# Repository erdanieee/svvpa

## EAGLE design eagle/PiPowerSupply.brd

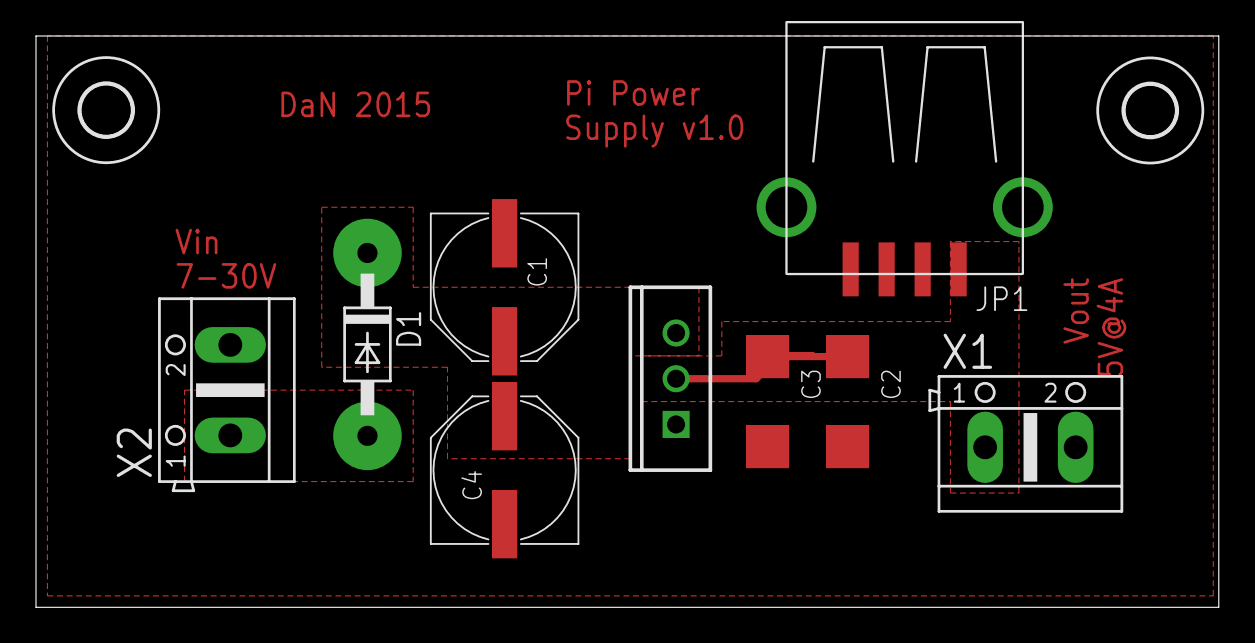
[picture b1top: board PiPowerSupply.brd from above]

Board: 2 copper layers, 65.7 x 31.7 mm, 11 parts (0 on the bottom side), 4 nets.

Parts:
C1, C4: 10u; PANASONIC_E
C2, C3: 10u; SMC_C
D1: 1N4004; DO41-10
H1, H2: MOUNT-HOLE2.8; 2,8
JP1: USB-A-S
U$1: V_REG_317SINK; TO220-ADJ
X1, X2: AK500/2

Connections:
GND: C1.-, C2.-, C3.-, C4.-, JP1.GND, U$1.ADJ, X1.2, X2.2
unnamed: D1.A, X2.1
VIN: C1.+, C4.+, D1.C, U$1.IN
VOUT: C2.+, C3.+, JP1.VBUS, U$1.OUT, X1.1

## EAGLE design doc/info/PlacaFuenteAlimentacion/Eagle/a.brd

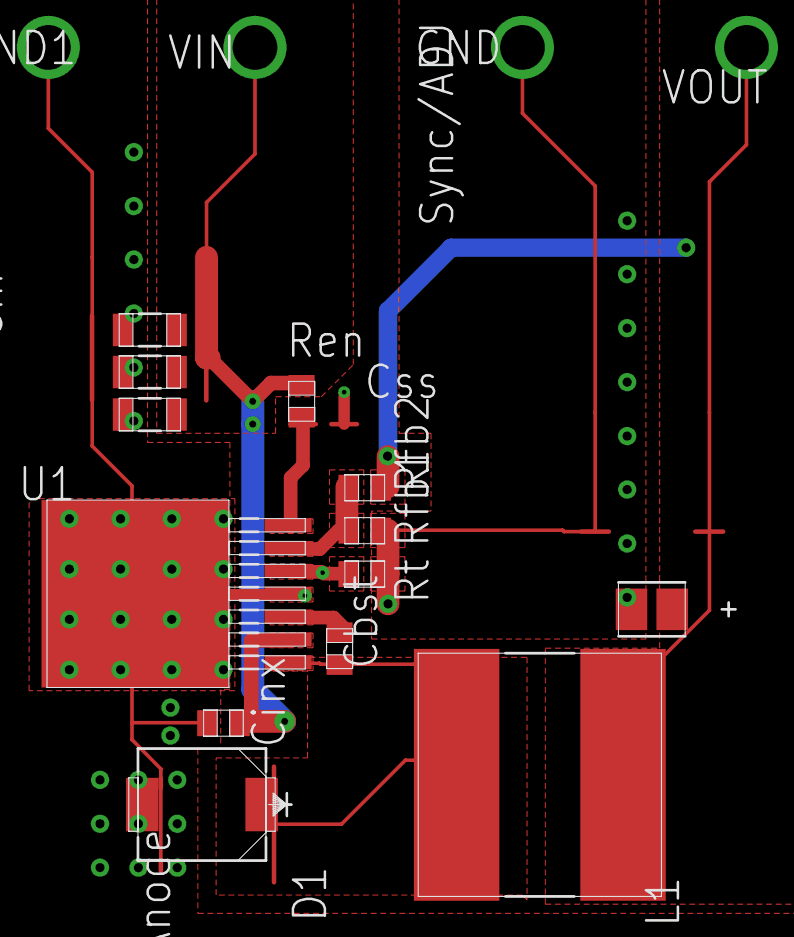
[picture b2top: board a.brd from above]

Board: 4 copper layers, 17 parts (0 on the bottom side), 7 nets.

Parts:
Cbst: 0805
Cin_1, Cin_2, Cin_3: 1206
Cinx: 0805
Cout: 3528-21
D1: SMC
GND, GND1: TP-1502
L1: SDR1307
Ren: 0805
Rfb1, Rfb2: 0805
Rt: 0805
U1: TJ7A
VIN: TP-1502
VOUT: TP-1502

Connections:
0: Cin_1.2, Cin_2.2, Cin_3.2, Cinx.2, Cout.2, D1.2, GND.1, GND1.1, Rfb1.2, Rt.2, U1.4, U1.8
1: Ren.1, U1.7
2: Cout.1, L1.2, Rfb1.1, Rfb2.1, Rfb2.2, U1.6, VOUT.1
3: Cin_1.1, Cin_2.1, Cin_3.1, Cinx.1, Ren.2, U1.2, VIN.1
4: Cbst.1, D1.1, L1.1, U1.1
5: Cbst.2, U1.3
6: Rt.1, U1.5

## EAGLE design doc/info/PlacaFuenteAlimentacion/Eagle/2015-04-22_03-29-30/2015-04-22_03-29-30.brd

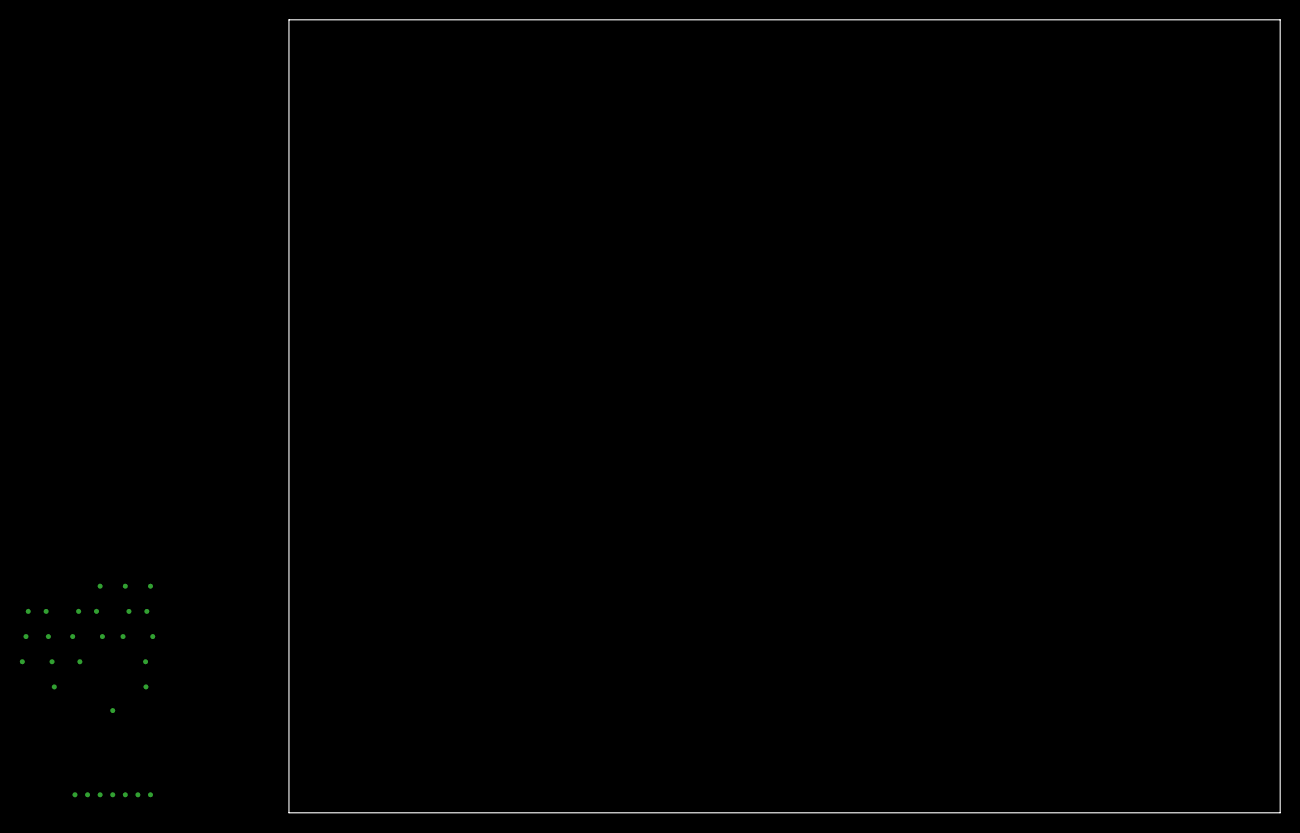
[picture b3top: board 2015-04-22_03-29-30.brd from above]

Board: 2 copper layers, 100.0 x 80.0 mm, 13 parts (0 on the bottom side), 6 nets, no tracks yet.

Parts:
CBST: 10nF; 0805
CIN: 4.7uF; 1206
CINX: 1uF; 0805
CIN_2, CIN_3: 4.7uF; 1206
COUT: 100uF; 3528-21
CSS: 39nF; 0805
D1: 700mV; SMC
GND: WB_GND
IOUT: WB_CURRENT_LOAD
L1: 10uH; SDR1307
U1: LM22679TJ-5.0/NOPB; TJ7A
VIN: WB_BATTERY

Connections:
0: CIN.2, CINX.2, CIN_2.2, CIN_3.2, COUT.2, CSS.2, D1.2, GND.1, IOUT.2, U1.4, U1.8, VIN.2
1: CSS.1, U1.7
2: COUT.1, IOUT.1, L1.2, U1.6
3: CIN.1, CINX.1, CIN_2.1, CIN_3.1, U1.2, VIN.1
4: CBST.1, D1.1, L1.1, U1.1
5: CBST.2, U1.3

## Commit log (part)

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2016-02-17 movido directorio bin fuera de www
2016-02-17 movido fichero con constantes para php y bash a directorio config
2016-02-17 modificaciones por defecto de las constantes para que funcione en la RPi
2016-02-17 mend
2016-02-17 modificado path ../config/ por constante CONFIG_DIR
2016-02-17 arreglado directorio que no existía
2016-02-17 borrado valores temporales de los ficheros de configuración
2016-02-17 sustituida variable que no existía por una constante
2016-02-17 añadidas librerías python de Adafruit
2016-02-17 archivos CONSTANTS movidos a sus directorios
2016-02-17 añadido RCLONE_CONFIG
2016-02-17 error en extensión
2016-02-18 ahora se envía email cuando no se puede acceder a la cámara
2016-02-19 En la hoja de cálcula ahora se insertan valores numéricos en lugar de cadenas de texto
2016-02-19 ahora sí está arreglado el asunto de la coma y el punto
2016-02-19 Arreglado problema al escribir números en hoja de google spreadsheet. El problema doble: - por una parte, el locate the python estaba en inglés y el locale de google en español, por lo que había prob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
    Para solucionarlo se han creado 2 funciones en el wrapper, uno para convertir a valores MySQL y otro para adaptarlo a script python.
2016-02-19 Cambiados permisos de los videos/imágenes que se graban al directorio www/motion
2016-02-19 Nuevo archivo de configuración de motion para una versión más reciente
2016-02-19 ahora permite enviar email a múltiples destinatarios
2016-02-26 Modificado el texto del email para que incluya el consumo de datos actual y el enlace para acceso remoto
2016-03-01 arreglado merge
2016-03-02 añadido inicial
2016-03-02 añadido alias de gmail para poner etiquetas automáticamente y variable para saber si el sistema tiene acceso remoto (IP pública) o no, y actuar en consecuencia
2016-03-02 cambiados permisos de ficheros python y añadiendo ejecutable para procesar comandos por email
2016-03-03 añadido ejemplo para checkear emails en cron
2016-03-04 añadida función enviar a google drive
2016-03-04 añadida función CMD_SVVPA ESTADO_DEL_SISTEMA
2016-03-04 Programas para enviar correo electrónico al iniciar el sistema
2016-03-04 requerimientos de cron y on_startup
2016-03-04 Añadido mecanismo para evitar que se use un fichero de configuración obsoleto
2016-03-07 cambio texto mínimo
2016-03-07 cambio exit por return para que no se cierre la shell cuando se ejecute desde la shell
2016-03-07 Añadido comando para iniciar, parar o pausar MOTION
2016-03-07 corregido nombre de ficheros
2016-03-08 Verificación del md5sum por texto en lugar de por número
2016-03-08 Actualizado el sistema de logger. Ahora se normaliza y se envía a un fichero
2016-03-09 Uso de librería gmail en python para mandar los emails
2016-03-09 corregido error sintáctico
2016-03-11 cambio de nombre del fichero
2016-03-11 Nueva función: Actualizar repositorio svvpa desde github
2016-03-11 unificado script para mandar mensajes al arrancar y parar el sistema
2016-03-11 Ahora sendEmailCameraLost se integra en el servicio SVVPA
2016-03-11 Añadido servicio SVVPA para controlar startup/shutdown del sistema y llamadas de scripts desde motion y cron
2016-03-11 Integración de todos los comandos que ejecuta SVVPA (a través MOTION, CRON, WEB o EMAILS) en un solo servicio
2016-03-11 Terminando de añadir servicio SVVPA-service. Corregidos algunos errores y cambiados los ejemplos cron.example y motion.conf
2016-03-11 Reescritura de la función free_space_up_to() para liberar espacio
2016-03-11 Cambiada cabecera del script para que se use la versión por defecto de python
2016-03-13 borradas constantes de gmail porque ahora s usa la librería
2016-03-13 se ignora el logrotate de usuario
2016-03-14 Error sintáctico
2016-03-14 Eliminando return del case, ya que no es una función y da error
2016-03-14 cambiado nombre de case y ruta completa del binario service
2016-03-14 añadido autocompletado para el servicio SVVPA-service
2016-03-14 añadidas instrucciones para usar el autocompletado del servicio SVVPA-service
2016-03-14 Codificación unicode del cuerpo del mensaje
2016-03-14 Convertidos varios strings a UTF8 y eliminado \r\n del subject de los emails, porque al parecer aparecen automáticamente cuando el subject es muy largo
2016-03-14 Eliminado buffer de python para que los prints sean en tiempo real. Modificado permiso y propietario de imágenes y vídeos, y errores menores
2016-03-14 Intento de solucionar problema al cerrar la conexión ssh remota cuando expira el tiempo
2016-03-15 modificación menor
2016-03-15 Nueva función para mandar emails
2016-03-16 Unificación en el envío de emails
2016-03-16 Modificado log para que no se duplique el mensaje de espacio disponible en disco
2016-03-16 Unificado _readBmp180 para que lea temperatura y humedad a la vez, imitando el funcionamiento de DHT22
2016-03-16 Ahora el servicio se inicia el último y se para el primero. También se ha modificado update_sensors para gestionar la unificación de _readBmp180
2016-03-16 Output en tiempo real para lectura de sensores
2016-03-16 Errores se envían a stderr
2016-03-16 Eliminada codificación unicode de los String, porque ya no es necesario si se define UTF8 en la cabecera
2016-03-18 Añadido ejemplo avconv que no pierde calidad
2016-03-18 Añadido de nuevo codificación unicode para las cadenas de texto, y arreglado el commando open/close ssh remoto
2016-03-28 No se pueden usar los 2 a la vez porque peta el buffer USB. Solución: bajar resolución, usar cámaras que soporten compresión (MPEG) y puede que también funcione si se usa un hub USB
2016-03-28 ahora se actualiza el uso antes de leerlo
2016-03-28 quitado final de línea \n
2016-04-01 cambiado repositorio gmail
2016-04-01 quitamos la etiqueta tempral de CMD_WORKING
2016-04-04 Motion necesita sudo para actualizar vnstat antes de mandar email con imagen
2016-04-06 arreglado problema al cerrar el servicio ssh y con los comandos que tardan mucho en procesarse
2016-04-06 tiempo de espera si no se puede enviar email es ahora incremental 2^n para n=(0,13)
2016-04-13 agrupación de notificaciones. Aún no está implementado el sistema de colas
2016-04-15 añadido BOT telegram para controlar SVVPA mediante telegrom messenger
2016-04-18 función añadir usuario completada
2016-04-19 Añadida función /motion (iniciar, parar o pausar detección de movimiento)
2016-04-19 Quitado los snapshot. Por ahora se usará fswebcam
2016-04-19 añadida función snapshot
2016-04-19 eliminado FIXME ya fixeado
2016-04-20 se ordena antes de comprobar la coincidencia entre CONSTANTS.sh y CONSTANTS.sh.example
2016-04-20 comprueba que la variable GOOGLE_DRIVE_CREDENTIALS está definida, sale si no es así
2016-04-20 añadidos requerimientos para instalar telepot y nodejs
2016-04-20 añadida función motion_check_status
2016-04-20 snapshot se mueve al directorio motion para poderlo localizar luego fácilmente, y que no dependa de la variable MOTION_TARGET que NO está definida en CONSTANTS.sh (solo está en motion.conf)
2016-04-20 añadida función open_ssh
2016-04-20 añadido sshpass para evitar problema con las keys
2016-04-23 migración a telepot 2.0, keyboards inline y todo empaquetado en una clase
2016-04-23 fix add user callback
2016-04-27 función /movimiento completada
2016-04-28 añadida función /ssh
2016-04-29 añadidos unos cuantos FIXMEs para que no se me olvide
2016-04-29 añadido python-mysqldb
2016-04-29 comando /sensores añadido
2016-05-01 funciones apagar y reiniciar añadidas
2016-05-06 vnstat ahora en bytes
2016-05-06 notificador de eventos (movimiento, startup/shutdown, cameralost, ...) mediante email y/o telegram
2016-05-06 añadida función notificación por email
2016-05-06 versión no funcional de notificator
2016-05-10 No se incluyen las credenciales de google drivegit add ../.gitignore
2016-05-10 v1.0
2016-05-11 imágenes se insertan en la base de datos y se suben automáticamente a google drive
2016-05-11 versión 1.0. Falta checkear a fondo
2016-05-12 función main ahora retorna el link de google drive
2016-05-12 upload_video ahora utiliza _google_drive_uploader en lugar de RClone
2016-05-12 Notificaciones unificadas en _notification.py
2016-05-12 unificación del notificador
2016-05-12 bug fixing
2016-05-15 añadido TODO
2016-05-15 minor bug fixing
2016-05-15 añadida comprobación periódica de telegram_bot
2016-05-15 eliminado un TODO
2016-05-15 arreglados problemas con los acnetos
2016-05-17 import MySQL table
2016-05-17 solucionado problema con los acentos
2016-05-17 ahora no imprime el link de google drive al finalizar
2016-05-17 link de google drive lo coge de MySQL, reboot y shutdown ahora van con un timer para que se lea el mensaje de telegram y no se reinicie constantemente
2016-05-17 modificación de tiempos
2016-05-17 usuario MOTION ahora tiene permisos sudo para ejecutar service
2016-05-18 arreglado problema con inlinequery
2016-05-18 el tamaño se almacena en bytes en MySQL
2016-05-20 nuevo sistema de obtención de credenciales
2016-05-20 ignore credentials
2016-05-20 WARNING si el fichero de configuración está obsoleto, en lugar de abortar!
2016-05-24 eliminado FIXME
2016-05-24 content type automáticamente establecido en función del archivo a enviar
2016-05-24 fix mysql query
2016-05-25 eliminada subida de datos a plotly
2016-05-25 fecha de modificación de la captura en el caption de la foto cuando se toma una instantánea
2016-05-25 maxsize y compress
2016-05-25 cambiado nombre de la hoja de cálculo
2016-05-26 agregados algunas tildes
2016-05-26 añadido comando shell
2016-05-26 shell en thread para evitar que se ejectute una y otra vez si falla algo...
2016-05-26 shell command no aparece en la ayuda
2016-06-07 Añadida función para subir vídeos más antiguos
2016-06-07 Ayuda ahora muestra link al documento SVVPA
2016-06-16 bug fix de la rotación de ficheros
2016-07-20 relax time ahora se configura en CONSTANTS.sh
2016-07-21 eliminado start/stop motion por la noche
2016-07-21 añadida notificación para inicio/parada del bot telegram
2016-09-07 added some documentation
2016-09-23 add power-saving info
2016-12-17 añadidos algunos TODO
2016-12-30 Corregido sensor de presión: ahora expresa en hPa equivalentes al nivel del mar. Añadida constante ALTITUDE
2016-12-30 _readDbmp180 ahora se lee sin sudo porque no hace falta y porque si no, se habre una subshell sin las varialbes de entorno (ALTITUDE)
2017-04-04 Añadido tiempo variable de refresco (relax) de los servidores de telegram
2017-04-06 añadida captura de excepción al procesar comandos
2017-04-07 Eliminado los de refresco telegram
2017-04-07 eliminado parámetro self de función update_time
2017-04-11 comando shell devuelve también código de retorno
2017-04-11 disminuida sensibilidad de motion a los cambios de luz
2017-04-14 ahora motion va por mmal
2017-04-24 motion.conf mmal
2017-05-04 añadida documentación para minirouter
2017-05-23 ahora las constantes se cargan directamente de CONSTANTS.sh; no es necesario modificarlo en cada instalación
2017-05-23 ahora tb se crean usuarios automáticamente
2017-05-23 eliminada variable MYSQL_SERVER
2017-05-23 eliminadas opciones para motion mmal
2017-05-23 añadido reinicio todos los días... pa porsi
2017-05-23 FIX cmd ayuda
2017-05-26 removed RCLONE
2017-06-06 Cambiado nombre del bot telegram, ya que por alguna razón los mensajes enviados por el bot no pueden tener su nombre (git add _telegram_bot.py ??)
2017-06-06 minor bug
2017-06-06 sudo fix
2017-06-06 eliminadas tildes de los print, porque dan problemas
2017-06-12 fichero de configuración iptables
2017-06-13 modificación fichero iptables-persistent
2017-06-13 archivos de configuración del minirouter
2017-06-13 eliminados varios TODOs
2017-06-14 se actualiza el tráfico de internet antes de mostrar el consumo actual
2017-06-14 delay antes de reiniciar el rooter
2017-06-14 moved
2017-06-16 sustituido sensor DHT22 por SI7021
2017-06-19 añadida función para reiniciar telegram después de una actualización
2017-06-19 testing
2017-08-30 Añadido sistema para para mmotion durante la noche
2017-08-31 aumentada sensibilidad
2017-08-31 minor changes
2017-08-31 añadida función para tomar fotos para el time lapse
2017-08-31 eliminado output para motion status y motion stop
2017-09-04 exit status codes fixed
2017-09-08 eliminada llamada a google_drive_uploader.py porque se subían dos veces las imágenes
2017-10-02 modificado lightswitch threshold
2017-10-02 codificación por defecto de python español, en lugar de ascii
2017-10-06 añadido sudo
2017-10-09 falta de orticultura
2018-01-06 reemplazo de función split (deprecated) por explode

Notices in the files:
parts and their libraries:
SparkFun-Connectors: Licensing: Creative Commons ShareAlike 4.0 International - https://creativecommons.org/licenses/by-sa/4.0
